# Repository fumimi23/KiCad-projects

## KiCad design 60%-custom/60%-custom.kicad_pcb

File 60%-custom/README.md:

# 60% Custom

## Keyboard layout

## Dependencies
- https://github.com/foostan/kbd
- https://github.com/keebio/Keebio-Parts.pretty

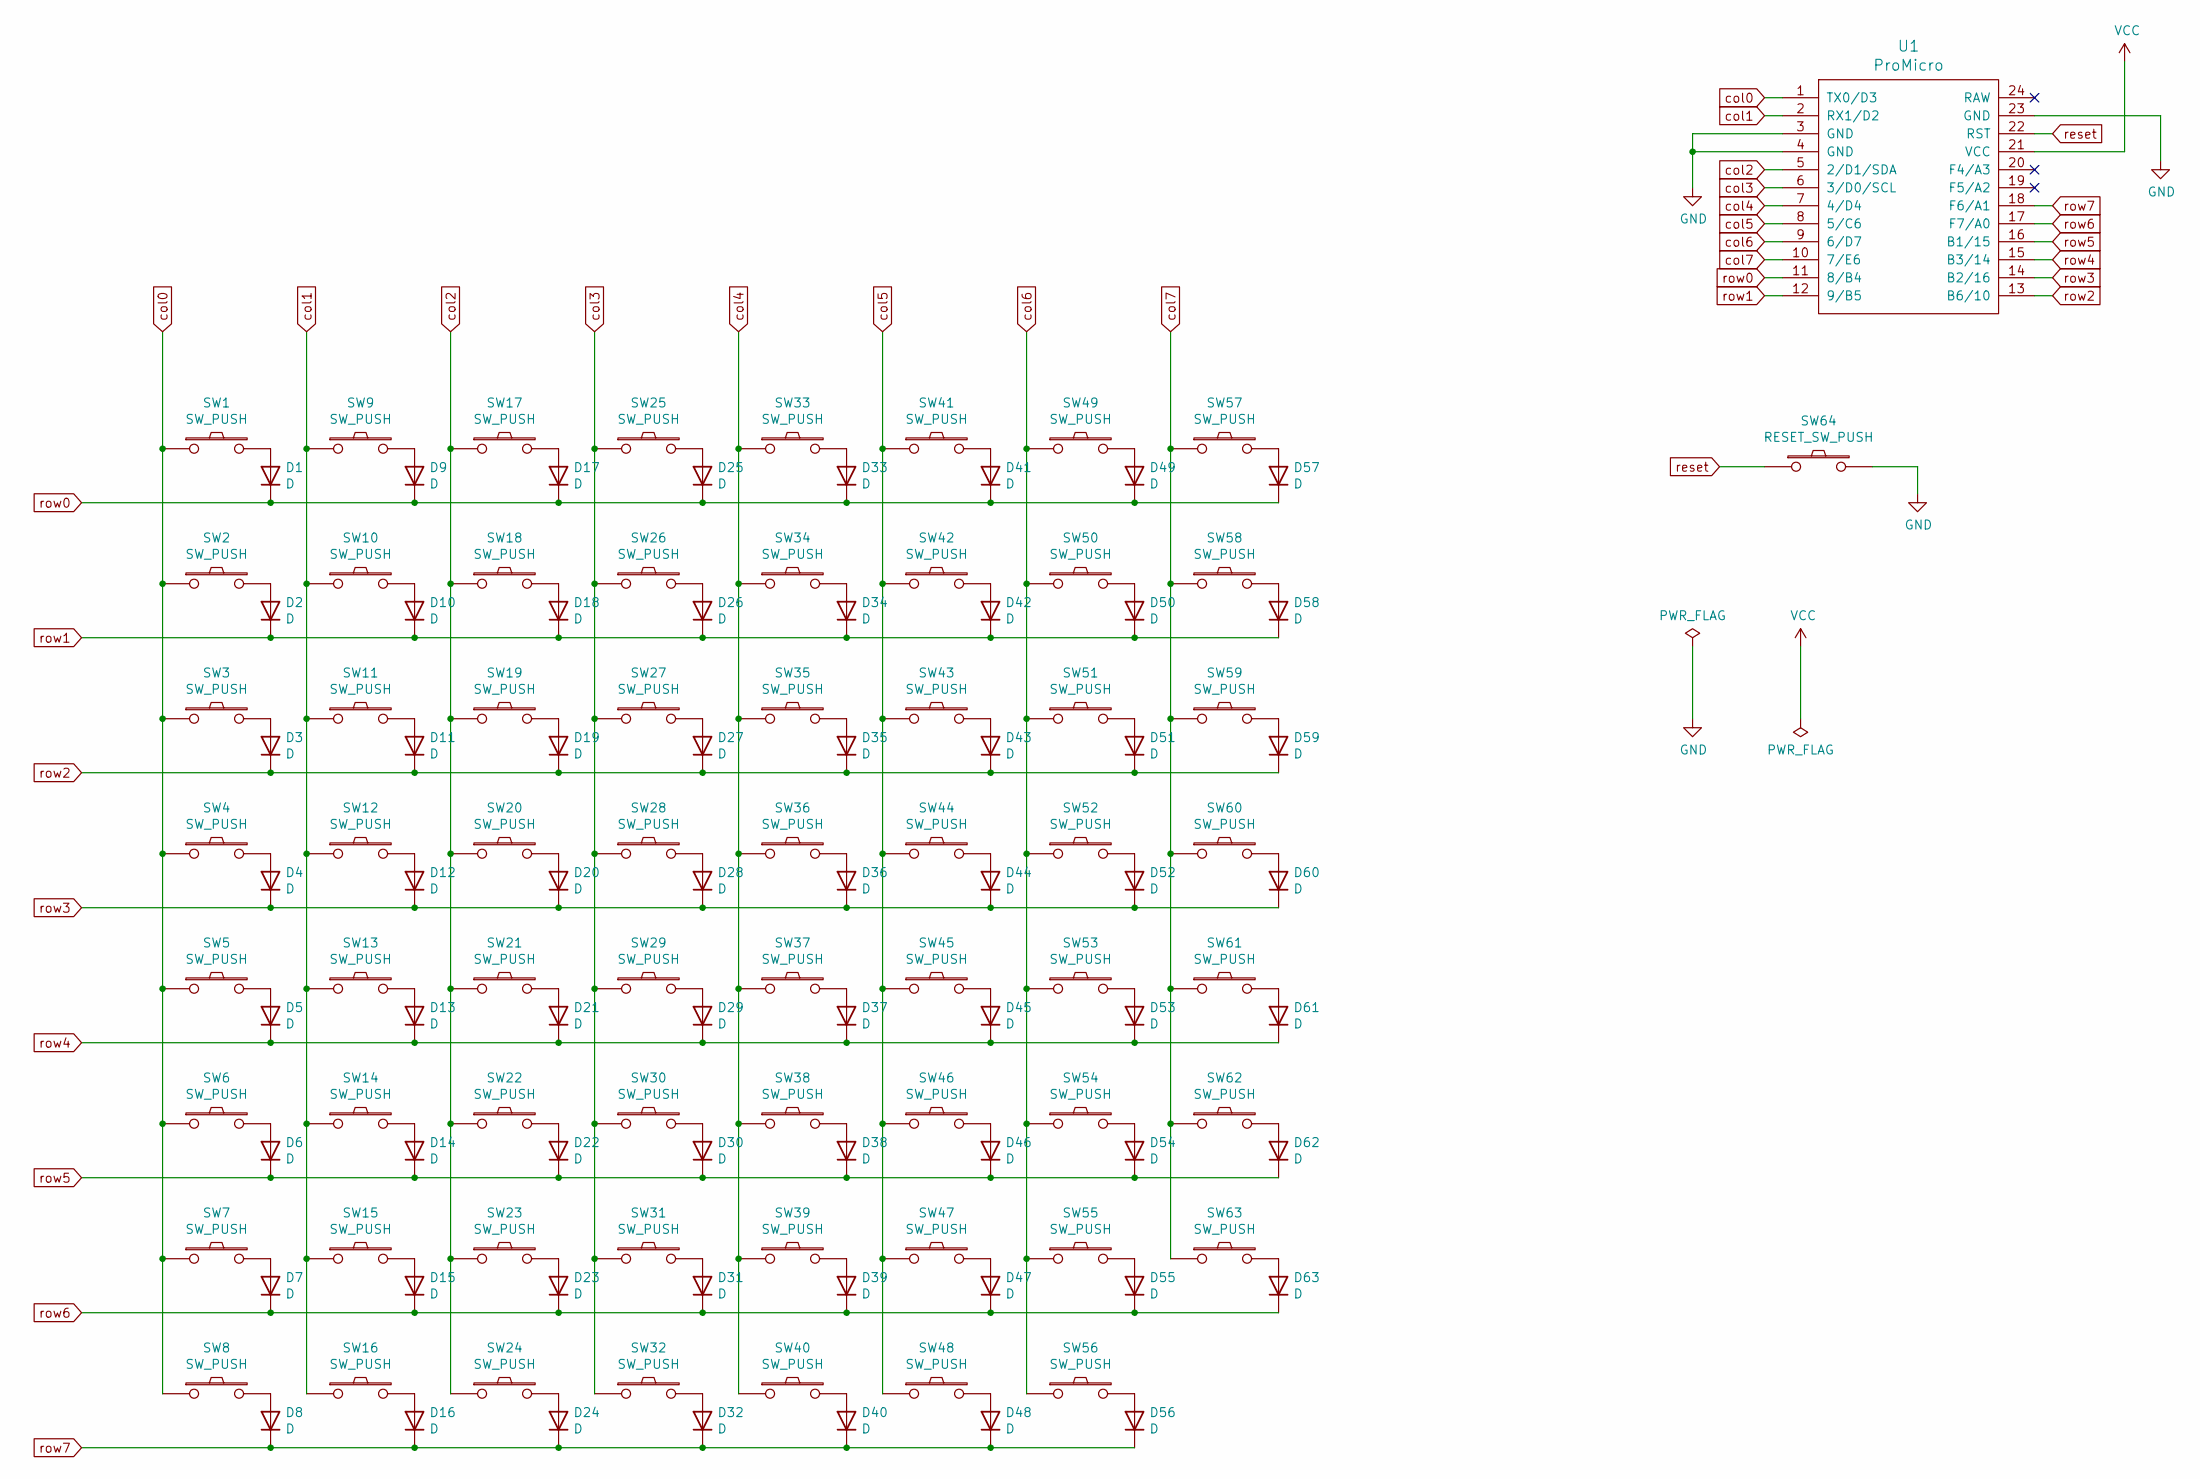
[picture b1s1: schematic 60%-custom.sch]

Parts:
D1, D2, D3, D4, D5, D6, D7, D8, D9, D10, D11, D12, D13, D14, D15, D16, D17, D18, D19, D20, D21, D22, D23, D24, D25, D26, D27, D28, D29, D30, D31, D32, D33, D34, D35, D36, D37, D38, D39, D40, D41, D42, D43, D44, D45, D46, D47, D48, D49, D50, D51, D52, D53, D54, D55, D56, D57, D58, D59, D60, D61, D62, D63: D; D3_TH_SMD
SW1, SW2, SW3, SW4, SW5, SW6, SW7, SW8, SW9, SW10, SW11, SW12, SW13, SW14, SW15, SW16, SW17, SW18, SW19, SW20, SW21, SW22, SW23, SW24, SW25, SW26, SW27, SW28, SW29, SW30, SW31, SW32, SW33, SW34, SW35, SW36, SW37, SW38, SW39, SW40, SW41, SW42, SW43, SW44, SW45, SW46, SW47, SW48, SW49, SW50, SW51, SW52, SW53, SW54, SW55, SW56, SW57, SW58, SW59, SW60, SW61, SW62, SW63: SW_PUSH; CherryMX_Hotswap
SW64: RESET_SW_PUSH; ResetSW_4P
U1: ProMicro; ArduinoProMicro

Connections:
GND: SW64.2, U1.3 (GND), U1.4 (GND), U1.23 (GND)
unnamed: D1.2 (A), SW1.2
unnamed: D2.2 (A), SW2.2
unnamed: D3.2 (A), SW3.2
unnamed: D4.2 (A), SW4.2
unnamed: D5.2 (A), SW5.2
unnamed: D6.2 (A), SW6.2
unnamed: D7.2 (A), SW7.2
unnamed: D8.2 (A), SW8.2
unnamed: D9.2 (A), SW9.2
unnamed: D10.2 (A), SW10.2
unnamed: D11.2 (A), SW11.2
unnamed: D12.2 (A), SW12.2
unnamed: D13.2 (A), SW13.2
unnamed: D14.2 (A), SW14.2
unnamed: D15.2 (A), SW15.2
unnamed: D16.2 (A), SW16.2
unnamed: D17.2 (A), SW17.2
unnamed: D18.2 (A), SW18.2
unnamed: D19.2 (A), SW19.2
unnamed: D20.2 (A), SW20.2
unnamed: D21.2 (A), SW21.2
unnamed: D22.2 (A), SW22.2
unnamed: D23.2 (A), SW23.2
unnamed: D24.2 (A), SW24.2
unnamed: D25.2 (A), SW25.2
unnamed: D26.2 (A), SW26.2
unnamed: D27.2 (A), SW27.2
unnamed: D28.2 (A), SW28.2
unnamed: D29.2 (A), SW29.2
unnamed: D30.2 (A), SW30.2
unnamed: D31.2 (A), SW31.2
unnamed: D32.2 (A), SW32.2
unnamed: D33.2 (A), SW33.2
unnamed: D34.2 (A), SW34.2
unnamed: D35.2 (A), SW35.2
unnamed: D36.2 (A), SW36.2
unnamed: D37.2 (A), SW37.2
unnamed: D38.2 (A), SW38.2
unnamed: D39.2 (A), SW39.2
unnamed: D40.2 (A), SW40.2
unnamed: D41.2 (A), SW41.2
unnamed: D42.2 (A), SW42.2
unnamed: D43.2 (A), SW43.2
unnamed: D44.2 (A), SW44.2
unnamed: D45.2 (A), SW45.2
unnamed: D46.2 (A), SW46.2
unnamed: D47.2 (A), SW47.2
unnamed: D48.2 (A), SW48.2
unnamed: D49.2 (A), SW49.2
unnamed: D50.2 (A), SW50.2
unnamed: D51.2 (A), SW51.2
unnamed: D52.2 (A), SW52.2
unnamed: D53.2 (A), SW53.2
unnamed: D54.2 (A), SW54.2
unnamed: D55.2 (A), SW55.2
unnamed: D56.2 (A), SW56.2
unnamed: D57.2 (A), SW57.2
unnamed: D58.2 (A), SW58.2
unnamed: D59.2 (A), SW59.2
unnamed: D60.2 (A), SW60.2
unnamed: D61.2 (A), SW61.2
unnamed: D62.2 (A), SW62.2
unnamed: D63.2 (A), SW63.2
VCC: U1.21 (VCC)
col0: SW1.1, SW2.1, SW3.1, SW4.1, SW5.1, SW6.1, SW7.1, SW8.1, U1.1 (TX0/D3)
col1: SW9.1, SW10.1, SW11.1, SW12.1, SW13.1, SW14.1, SW15.1, SW16.1, U1.2 (RX1/D2)
col2: SW17.1, SW18.1, SW19.1, SW20.1, SW21.1, SW22.1, SW23.1, SW24.1, U1.5 (2/D1/SDA)
col3: SW25.1, SW26.1, SW27.1, SW28.1, SW29.1, SW30.1, SW31.1, SW32.1, U1.6 (3/D0/SCL)
col4: SW33.1, SW34.1, SW35.1, SW36.1, SW37.1, SW38.1, SW39.1, SW40.1, U1.7 (4/D4)
col5: SW41.1, SW42.1, SW43.1, SW44.1, SW45.1, SW46.1, SW47.1, SW48.1, U1.8 (5/C6)
col6: SW49.1, SW50.1, SW51.1, SW52.1, SW53.1, SW54.1, SW55.1, SW56.1, U1.9 (6/D7)
col7: SW57.1, SW58.1, SW59.1, SW60.1, SW61.1, SW62.1, SW63.1, U1.10 (7/E6)
reset: SW64.1, U1.22 (RST)
row0: D1.1 (K), D9.1 (K), D17.1 (K), D25.1 (K), D33.1 (K), D41.1 (K), D49.1 (K), D57.1 (K), U1.11 (8/B4)
row1: D2.1 (K), D10.1 (K), D18.1 (K), D26.1 (K), D34.1 (K), D42.1 (K), D50.1 (K), D58.1 (K), U1.12 (9/B5)
row2: D3.1 (K), D11.1 (K), D19.1 (K), D27.1 (K), D35.1 (K), D43.1 (K), D51.1 (K), D59.1 (K), U1.13 (B6/10)
row3: D4.1 (K), D12.1 (K), D20.1 (K), D28.1 (K), D36.1 (K), D44.1 (K), D52.1 (K), D60.1 (K), U1.14 (B2/16)
row4: D5.1 (K), D13.1 (K), D21.1 (K), D29.1 (K), D37.1 (K), D45.1 (K), D53.1 (K), D61.1 (K), U1.15 (B3/14)
row5: D6.1 (K), D14.1 (K), D22.1 (K), D30.1 (K), D38.1 (K), D46.1 (K), D54.1 (K), D62.1 (K), U1.16 (B1/15)
row6: D7.1 (K), D15.1 (K), D23.1 (K), D31.1 (K), D39.1 (K), D47.1 (K), D55.1 (K), D63.1 (K), U1.17 (F7/A0)
row7: D8.1 (K), D16.1 (K), D24.1 (K), D32.1 (K), D40.1 (K), D48.1 (K), D56.1 (K), U1.18 (F6/A1)

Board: 2 copper layers, 128 parts (0 on the bottom side), 81 nets, no tracks yet.

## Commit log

2024-08-31 feat: add project
2024-08-31 chore add gitignore
2024-08-31 update: delete backup file
2024-08-31 update: update gitignore
2024-08-31 docs: add README
2024-08-31 docs: update README
